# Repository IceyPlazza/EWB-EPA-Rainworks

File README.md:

<h1> For Visitors / New Members: </h1>

- Please browse through the key presentations folder to familiarize yourself with the general goal of Rainworks!
- Having some background in Java or C++ would assist you immensely if you're joining the CS Team.
- main branch is our last working version, main_revamp_WIP branch is our experimental/work-in-progress branch
- Please browse through the .ino files in both our main branch and WIP branch; documentation should help make understanding the code intuitive

<h1>For Returning Members:</h1>

- Glad to have you back! New tasks will be assigned to you every meeting depending on number of members in attendance and project progress
- Instructions to debug the Arduino can be found in arduino_debug.md
- Thingspeak overview for data collection can be found in thingspeak_data_collection.md
- Additional helpful resources in resources.md

<h1> NEW FOR 2026-2027 </h1>

All teams will now be using GitHub for version control!

<h1>Contact me if you have any questions! (Or send me code):</h1>

- iven.chen@vanderbilt.edu

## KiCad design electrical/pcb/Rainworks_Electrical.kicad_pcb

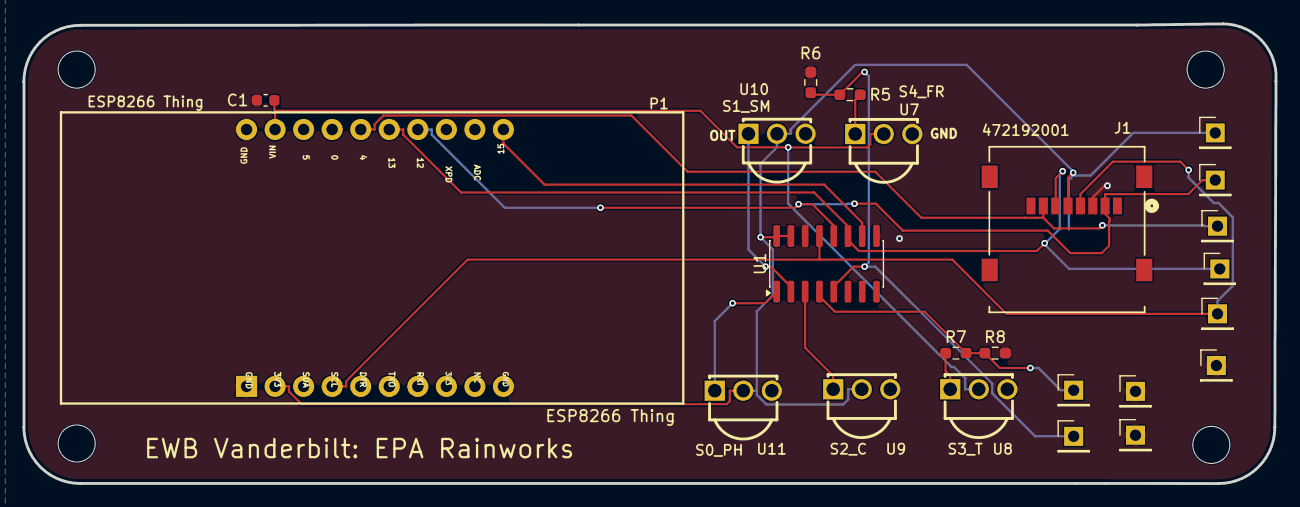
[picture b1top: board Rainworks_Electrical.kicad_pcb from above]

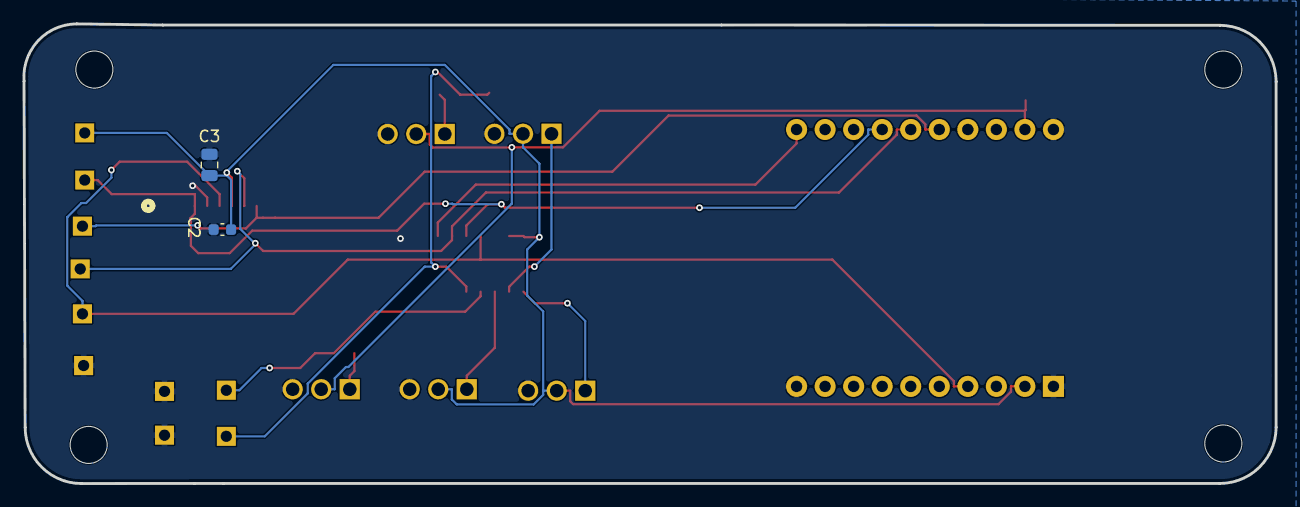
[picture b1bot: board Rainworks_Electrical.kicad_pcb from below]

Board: 2 copper layers, 111.4 x 40.9 mm, 29 parts (2 on the bottom side), 15 nets.

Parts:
C1: 100nF; C_0603_1608Metric
C2: 100 nF; C_0603_1608Metric
C3: 10 uF; C_0805_2012Metric
Hole_gge5569: Hole_gge5569
Hole_gge5584: Hole_gge5584
Hole_gge5599: Hole_gge5599
Hole_gge5614: Hole_gge5614
J1: 472192001; CONN_47219-2001_MOL
P1: ESP8266 Thing; ESP8266 THING
R5, R7: 15k; R_0603_1608Metric_Pad0.98x0.95mm_HandSolder
R6, R8: 10k; R_0603_1608Metric_Pad0.98x0.95mm_HandSolder
TP1: TURB; PinHeader_1x01_P2.54mm_Vertical
TP2: FR; PinHeader_1x01_P2.54mm_Vertical
TP3, TP4, TP10: GND; PinHeader_1x01_P2.54mm_Vertical
TP5: SDVDD; PinHeader_1x01_P2.54mm_Vertical
TP6: MOSI; PinHeader_1x01_P2.54mm_Vertical
TP7: MISO; PinHeader_1x01_P2.54mm_Vertical
TP8: SCLK; PinHeader_1x01_P2.54mm_Vertical
TP9: CS; PinHeader_1x01_P2.54mm_Vertical
U1: MCP3008; SOIC-16_3.9x9.9mm_P1.27mm
U7: S4_FR; SENSOR-TH_TSOP32238
U8: S3_T; SENSOR-TH_TSOP32238
U9: S2_C; SENSOR-TH_TSOP32238
U10: S1_SM; SENSOR-TH_TSOP32238
U11: S0_PH; SENSOR-TH_TSOP32238

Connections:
/3V3_VDD: C2.1, C3.1, J1.4 (5), P1.12 (3V3), TP5.1 (1_1), U1.15 (VREF), U1.16 (VDD), U9.2 (VDD), U10.2 (VDD), U11.2 (VDD)
/CH0_ADC: U1.1 (CH0), U11.1 (OUT)
/CH1_ADC: U1.2 (CH1), U10.1 (OUT)
/CH2_ADC: U1.3 (CH2), U9.1 (OUT)
/CH3_ADC: R7.2, R8.1, TP1.1 (1_1), U1.4 (CH3)
/CH4_ADC: R5.2, R6.1, TP2.1 (1_1), U1.5 (CH4)
/S3_T_VOUT: R7.1, U8.1 (OUT)
/S4_FR_VOUT: R5.1, U7.1 (OUT)
/SD_CS_SPI: J1.2 (7), P1.5 (4), TP9.1 (1_1)
/SD_MISO_SPI: J1.7 (2), P1.7 (12), TP7.1 (1_1), U1.12 (DOUT)
/SD_MOSI_SPI: J1.3 (6), P1.6 (13), TP6.1 (1_1), U1.11 (DIN)
/SD_SCLK_SPI: J1.5 (4), P1.14 (SCL), TP8.1 (1_1), U1.13 (CLK)
/VIN_5V0_MCU: C1.1, P1.2 (VIN), U7.2 (VDD), U8.2 (VDD)
GND: C1.2, C2.2, C3.2, J1.6 (3), P1.1 (GND), P1.11 (GND), P1.20 (GND), R6.2, R8.2, TP3.1 (1_1), TP4.1 (1_1), TP10.1 (1_1), U1.9 (DGND), U1.14 (AGND), U7.3 (GND), U8.3 (GND), U9.3 (GND), U10.3 (GND), U11.3 (GND)
unnamed: P1.10 (15), U1.10 (SHDN!CS)

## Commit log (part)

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2025-09-22 Add files via upload
    Latest code as of start of Fall 2025 semester.
2025-09-22 Add resources for ESP8266 programming and components
2025-09-22 Add data collection documentation for Thingspeak
    Documented the use of Thingspeak for data collection with various sensors.
2025-09-23 Add instructions for uploading code and reading serial messages
    Added detailed steps for uploading code to the board and reading serial messages.
2025-09-26 Update resources.md with SD Library link
    Added SD Library documentation link to resources.
2025-10-13 Add agenda for October 14, 2025
2025-10-17 New logic, finalized write, working on read
2025-10-31 Refactor code structure and add comments
2025-10-31 Refactor byte reading and combining logic
2025-11-05 added method descriptions
2025-11-05 Added SD card methods
2025-11-05 Rename and restructure SD reading functions
    Refactor SD reading functions to improve structure and readability.
2025-11-05 Refactor rainworks sketch for better structure
    Refactored the rainworks sketch to improve structure and functionality. Added methods for reading and writing to SD card, handling WiFi connections, and managing sensor data.
2025-11-07 Fix initializeSD()
2025-11-07 Refactor SD card file handling and initialization
    Removed redundant file deletion calls and added retry logic for SD card initialization.
2025-11-12 Refactor rainworks code for clarity and functionality
2025-11-12 Moved back to fixed time interval data collection times.
    Updated deep sleep time and modified sensor reading logic.
2025-11-12 Revise readAllFromSD function documentation
    Update function documentation to reflect future changes.
2025-11-14 Modified connectWifi() to return a Boolean
2025-11-14 Allows writeMain to see if WiFi is connected.
2025-11-14 Progress on writeMain()
2025-11-19 Fixed most compiler errors, fixed return type for arrays to be pointers.
2026-01-18 Added key presentations for ease of access
2026-01-18 Add arduino_debug.md file
2026-01-18 Add README content for new and returning members
    Added introductory information for visitors and returning members.
2026-01-18 Update README with returning members section
2026-01-18 Fix email formatting in README.md
2026-01-18 Improve formatting in arduino_debug.md
    Updated formatting and headings in the Arduino debug documentation.
2026-01-18 Refactor Thingspeak data collection documentation
    Updated formatting and structure of the Thingspeak data collection document.
2026-01-18 Update data collection items in documentation
    Removed Total Dissolved Solids and Microplastics from the data collection list.
2026-01-18 Refactor resources.md with improved structure
    Updated resources section with new formatting and links.
2026-01-18 Update README with Arduino and Thingspeak resources
    Added debugging and data collection instructions.
2026-01-21 IT COMPILES???????
2026-01-21 Rename rainworks_10-21-2025_WIP.ino to rainworks_main.ino
    CODE COMPILES????
2026-02-04 Using Wowki to debug SD methods, debug in progress
2026-02-25 Fix memcpy usage in splitBytes and combineBytes
2026-02-25 Update splitBytes to use pointer for byte output
    Refactor splitBytes function to use pointer for output.
2026-02-25 Change splitBytes to use array for byte storage
    Refactor byte splitting to use an array instead of a pointer.
2026-02-25 Clean up commented documentation in rainworks_main.ino
    Removed commented-out documentation blocks for several functions to clean up the code.
2026-02-25 Refactor sensor reading functions and usage
    Refactor readSensors and readFromSD functions to use pointers for sensor values. Update writeMain to directly use sensorValues array.
2026-02-25 Adjust ThingSpeak delay to 15 seconds
2026-03-17 Improve documentation for readAllFromSD and readFromSD
    Updated function documentation to clarify parameters and return values.
2026-03-17 Add simulator code
2026-04-14 Refactor SD card handling and update functions
2026-04-15 Add upload_and_debug.md file
2026-04-15 Add README.md for project guidelines and resources
2026-04-15 Add Thingspeak data collection documentation
    Documented the use of Thingspeak for data collection with ESP8266 and listed relevant resources.
